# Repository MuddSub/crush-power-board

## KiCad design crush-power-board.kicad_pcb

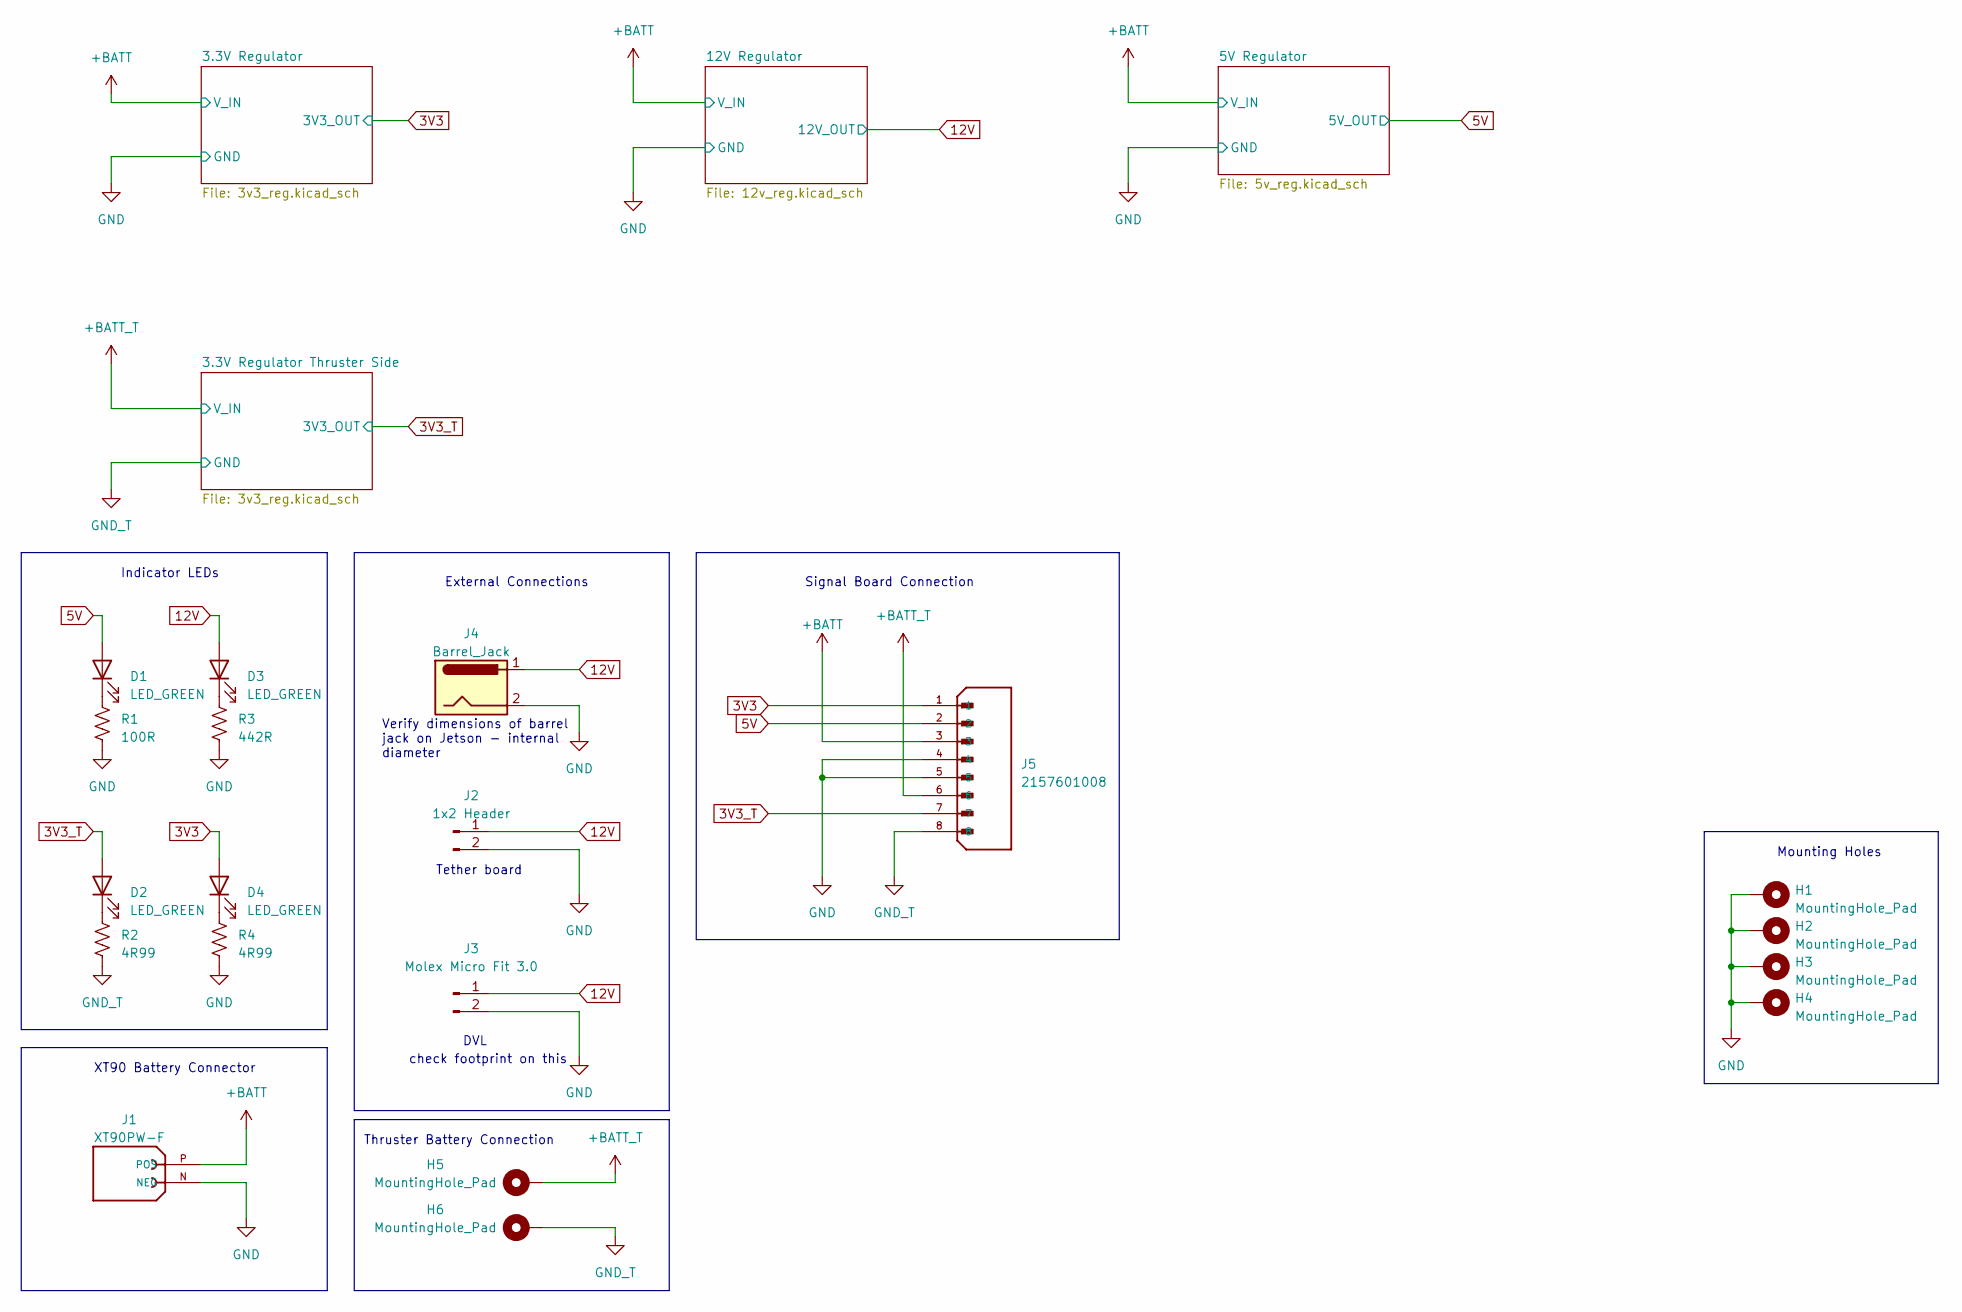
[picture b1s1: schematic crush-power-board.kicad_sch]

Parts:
D1, D2, D3, D4: LED_GREEN; LED_0603_1608Metric
H1, H2, H3, H4: MountingHole_Pad; MountingHole_3.7mm_Pad_Via
H5, H6: MountingHole_Pad; MountingHole_4.5mm_Pad_Via
J1: XT90PW-F; AMASS_XT90PW-F; PARTREV V00
J2: 1x2 Header; PinHeader_1x02_P2.54mm_Vertical
J3: Molex Micro Fit 3.0; Molex_Micro-Fit_3.0_43045-0212_2x01_P3.00mm_Vertical
J4: Barrel_Jack; BarrelJack_Horizontal
J5: 2157601008; MOLEX_2157601008; PARTREV A1
R1: 100R; R_0603_1608Metric
R2, R4: 4R99; R_0603_1608Metric
R3: 442R; R_0603_1608Metric

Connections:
3V3: D4.2 (A), J5.1; also elsewhere on the board
3V3_T: D2.2 (A), J5.7; also elsewhere on the board
5V: D1.2 (A), J5.2; also elsewhere on the board
12V: D3.2 (A), J2.1, J3.1, J4.1; also elsewhere on the board
+BATT: J1.P (POS), J5.3; also elsewhere on the board
+BATT_T: H5.1, J5.6; also elsewhere on the board
GND: H1.1, H2.1, H3.1, H4.1, J1.N (NEG), J2.2, J3.2, J4.2, J5.4, J5.5, R1.2, R3.2, R4.2; also elsewhere on the board
GND1: H6.1, J5.8, R2.2; also elsewhere on the board
unnamed: D1.1 (K), R1.1
unnamed: D2.1 (K), R2.1
unnamed: D3.1 (K), R3.1
unnamed: D4.1 (K), R4.1

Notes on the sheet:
check footprint on this
Indicator LEDs
Mounting Holes
DVL
Signal Board Connection
External Connections
XT90 Battery Connector
Thruster Battery Connection
Verify dimensions of barrel jack on Jetson - internal diameter
Tether board

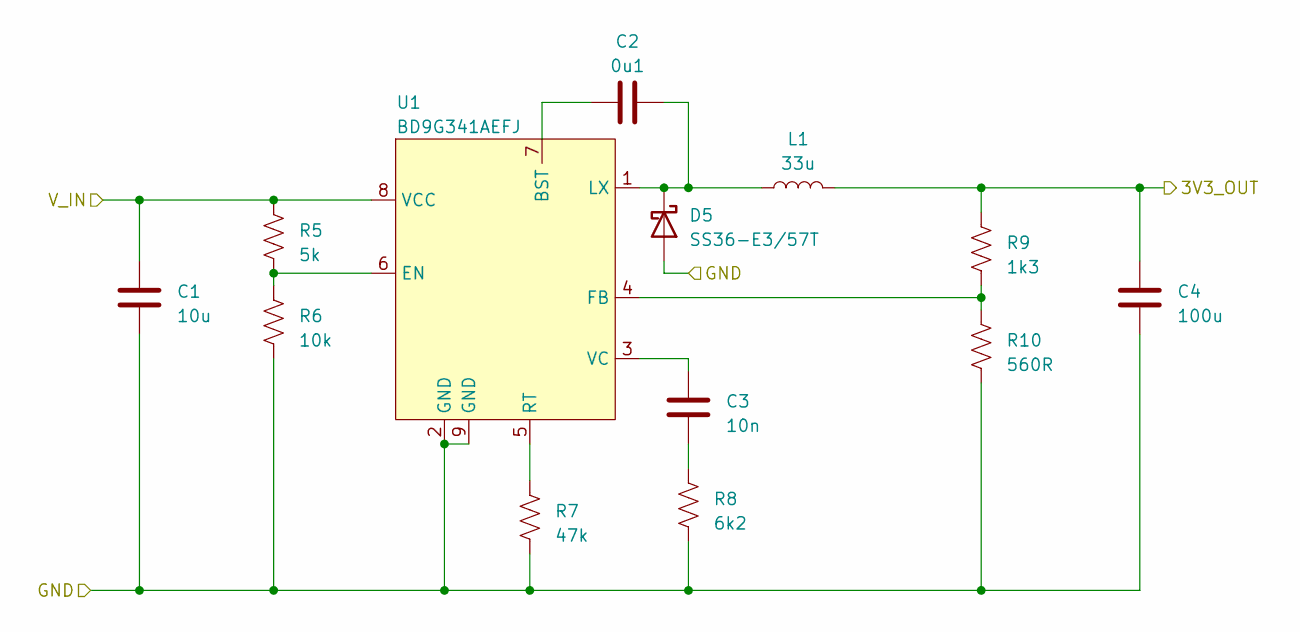
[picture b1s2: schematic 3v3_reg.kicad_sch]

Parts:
C1: 10u; C_0603_1608Metric
C2: 0u1; C_0603_1608Metric
C3: 10n; C_0603_1608Metric
C4: 100u; C_1206_3216Metric
D5: SS36-E3/57T; DIODE_DO214AB
L1: 33u; IND_#B953AS-330M=P3
R5: 5k; R_0603_1608Metric
R6: 10k; R_0603_1608Metric
R7: 47k; R_0603_1608Metric
R8: 6k2; R_0603_1608Metric
R9: 1k3; R_0603_1608Metric
R10: 560R; R_0603_1608Metric
U1: BD9G341AEFJ; SOIC127P600X100-9N

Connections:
3V3: C4.1, L1.2, R9.1; also elsewhere on the board
+BATT: C1.1, R5.1, U1.8 (VCC); also elsewhere on the board
GND: C1.2, C4.2, D5.2 (A), R6.2, R7.2, R8.2, R10.2, U1.2 (GND), U1.9 (GND); also elsewhere on the board
unnamed: C3.2, R8.1
unnamed: C2.2, D5.1 (K), L1.1, U1.1 (LX)
unnamed: C2.1, U1.7 (BST)
unnamed: R5.2, R6.1, U1.6 (EN)
unnamed: R9.2, R10.1, U1.4 (FB)
unnamed: R7.1, U1.5 (RT)
unnamed: C3.1, U1.3 (VC)

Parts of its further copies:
C45: 10u; C_0603_1608Metric
C46: 0u1; C_0603_1608Metric
C47: 10n; C_0603_1608Metric
C48: 100u; C_1206_3216Metric
D6: SS36-E3/57T; DIODE_DO214AB
L4: 33u; IND_#B953AS-330M=P3
R33: 5k; R_0603_1608Metric
R34: 10k; R_0603_1608Metric
R35: 47k; R_0603_1608Metric
R36: 6k2; R_0603_1608Metric
R37: 1k3; R_0603_1608Metric
R38: 560R; R_0603_1608Metric
U4: BD9G341AEFJ; SOIC127P600X100-9N

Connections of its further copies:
3V3_T: C48.1, L4.2, R37.1; also elsewhere on the board
+BATT_T: C45.1, R33.1, U4.8 (VCC); also elsewhere on the board
GND1: C45.2, C48.2, D6.2 (A), R34.2, R35.2, R36.2, R38.2, U4.2 (GND), U4.9 (GND); also elsewhere on the board
unnamed: C47.2, R36.1
unnamed: C46.2, D6.1 (K), L4.1, U4.1 (LX)
unnamed: C46.1, U4.7 (BST)
unnamed: R33.2, R34.1, U4.6 (EN)
unnamed: R37.2, R38.1, U4.4 (FB)
unnamed: R35.1, U4.5 (RT)
unnamed: C47.1, U4.3 (VC)

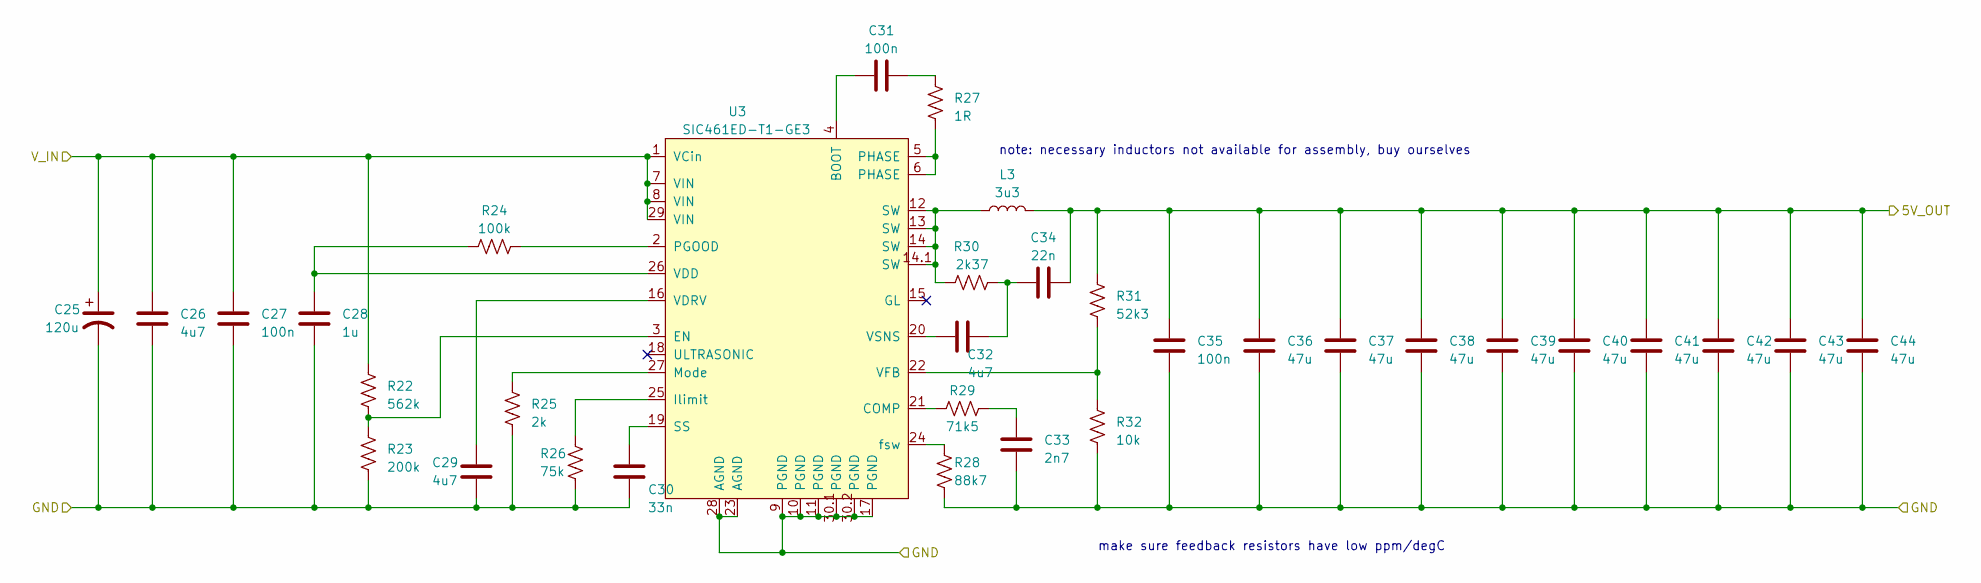
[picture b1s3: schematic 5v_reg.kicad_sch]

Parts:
C25: 120u; CP_Radial_D8.0mm_P3.50mm
C26: 4u7; C_0603_1608Metric
C27, C35: 100n; C_0603_1608Metric
C28: 1u; C_0603_1608Metric
C29, C32: 4u7; C_0805_2012Metric
C30: 33n; C_0603_1608Metric
C31: 100n; C_0402_1005Metric
C33: 2n7; C_0603_1608Metric
C34: 22n; C_0402_1005Metric
C36, C37, C38, C39, C40, C41, C42, C43, C44: 47u; C_1210_3225Metric
L3: 3u3; IND_IHLP-6767GZ_VIS-M
R22: 562k; R_0603_1608Metric
R23: 200k; R_0603_1608Metric
R24: 100k; R_0603_1608Metric
R25: 2k; R_0603_1608Metric
R26: 75k; R_0603_1608Metric
R27: 1R; R_0402_1005Metric
R28: 88k7; R_0603_1608Metric
R29: 71k5; R_0402_1005Metric
R30: 2k37; R_0402_1005Metric
R31: 52k3; R_0603_1608Metric
R32: 10k; R_0603_1608Metric
U3: SIC461ED-T1-GE3; CONV_SIC461ED-T1-GE3; PARTREV M

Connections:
5V: C34.2, C35.1, C36.1, C37.1, C38.1, C39.1, C40.1, C41.1, C42.1, C43.1, C44.1, L3.2, R31.1; also elsewhere on the board
+BATT: C25.1, C26.2, C27.2, R22.2, U3.1 (VCin), U3.7 (VIN), U3.8 (VIN), U3.29 (VIN); also elsewhere on the board
GND: C25.2, C26.1, C27.1, C28.1, C29.1, C30.1, C33.2, C35.2, C36.2, C37.2, C38.2, C39.2, C40.2, C41.2, C42.2, C43.2, C44.2, R23.1, R25.2, R26.2, R28.2, R32.2, U3.9 (PGND), U3.10 (PGND), U3.11 (PGND), U3.17 (PGND), U3.23 (AGND), U3.28 (AGND), U3.30.1 (PGND), U3.30.2 (PGND); also elsewhere on the board
unnamed: C31.2, R27.2
unnamed: C32.2, C34.1, R30.2
unnamed: C33.1, R29.2
unnamed: L3.1, R30.1, U3.12 (SW), U3.13 (SW), U3.14 (SW), U3.14.1 (SW)
unnamed: R27.1, U3.5 (PHASE), U3.6 (PHASE)
unnamed: C31.1, U3.4 (BOOT)
unnamed: R29.1, U3.21 (COMP)
unnamed: R22.1, R23.2, U3.3 (EN)
unnamed: R26.1, U3.25 (Ilimit)
unnamed: R25.1, U3.27 (Mode)
unnamed: R24.2, U3.2 (PGOOD)
unnamed: C30.2, U3.19 (SS)
unnamed: C28.2, R24.1, U3.26 (VDD)
unnamed: C29.2, U3.16 (VDRV)
unnamed: R31.2, R32.1, U3.22 (VFB)
unnamed: C32.1, U3.20 (VSNS)
unnamed: R28.1, U3.24 (fsw)

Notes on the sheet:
make sure feedback resistors have low ppm/degC
note: necessary inductors not available for assembly, buy ourselves

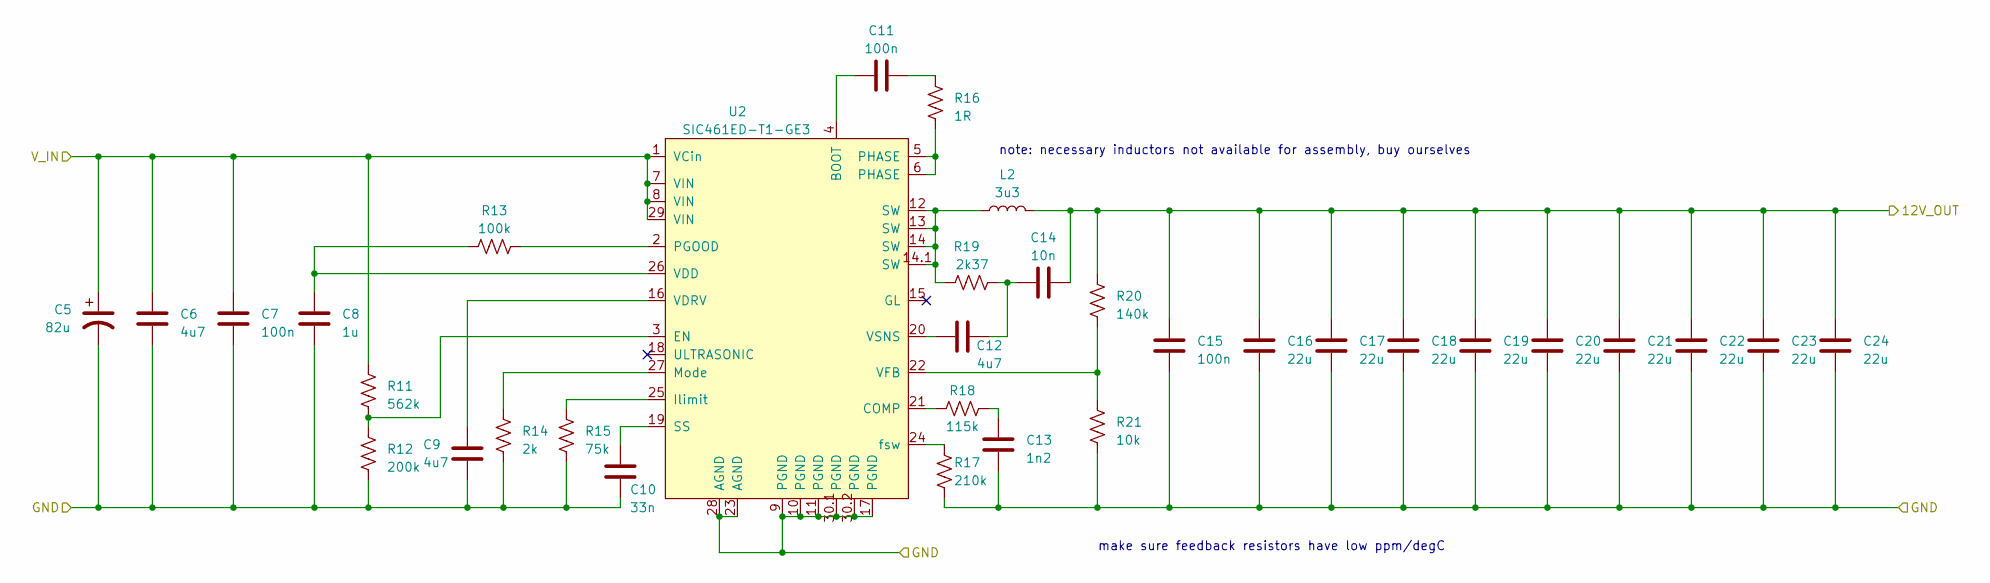
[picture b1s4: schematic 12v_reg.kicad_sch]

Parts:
C5: 82u; CP_Radial_D8.0mm_P3.50mm
C6: 4u7; C_0603_1608Metric
C7, C15: 100n; C_0603_1608Metric
C8: 1u; C_0603_1608Metric
C9, C12: 4u7; C_0805_2012Metric
C10: 33n; C_0603_1608Metric
C11: 100n; C_0402_1005Metric
C13: 1n2; C_0603_1608Metric
C14: 10n; C_0402_1005Metric
C16, C17, C18, C19, C20, C21, C22, C23, C24: 22u; C_1210_3225Metric
L2: 3u3; IND_IHLP-6767GZ_VIS-M
R11: 562k; R_0603_1608Metric
R12: 200k; R_0603_1608Metric
R13: 100k; R_0603_1608Metric
R14: 2k; R_0603_1608Metric
R15: 75k; R_0603_1608Metric
R16: 1R; R_0402_1005Metric
R17: 210k; R_0603_1608Metric
R18: 115k; R_0402_1005Metric
R19: 2k37; R_0402_1005Metric
R20: 140k; R_0603_1608Metric
R21: 10k; R_0603_1608Metric
U2: SIC461ED-T1-GE3; CONV_SIC461ED-T1-GE3; PARTREV M

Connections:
12V: C14.2, C15.1, C16.1, C17.1, C18.1, C19.1, C20.1, C21.1, C22.1, C23.1, C24.1, L2.2, R20.1; also elsewhere on the board
+BATT: C5.1, C6.2, C7.2, R11.2, U2.1 (VCin), U2.7 (VIN), U2.8 (VIN), U2.29 (VIN); also elsewhere on the board
GND: C5.2, C6.1, C7.1, C8.1, C9.1, C10.1, C13.2, C15.2, C16.2, C17.2, C18.2, C19.2, C20.2, C21.2, C22.2, C23.2, C24.2, R12.1, R14.2, R15.2, R17.2, R21.2, U2.9 (PGND), U2.10 (PGND), U2.11 (PGND), U2.17 (PGND), U2.23 (AGND), U2.28 (AGND), U2.30.1 (PGND), U2.30.2 (PGND); also elsewhere on the board
unnamed: C11.2, R16.2
unnamed: C12.2, C14.1, R19.2
unnamed: C13.1, R18.2
unnamed: L2.1, R19.1, U2.12 (SW), U2.13 (SW), U2.14 (SW), U2.14.1 (SW)
unnamed: R16.1, U2.5 (PHASE), U2.6 (PHASE)
unnamed: C11.1, U2.4 (BOOT)
unnamed: R18.1, U2.21 (COMP)
unnamed: R11.1, R12.2, U2.3 (EN)
unnamed: R15.1, U2.25 (Ilimit)
unnamed: R14.1, U2.27 (Mode)
unnamed: R13.2, U2.2 (PGOOD)
unnamed: C10.2, U2.19 (SS)
unnamed: C8.2, R13.1, U2.26 (VDD)
unnamed: C9.2, U2.16 (VDRV)
unnamed: R20.2, R21.1, U2.22 (VFB)
unnamed: C12.1, U2.20 (VSNS)
unnamed: R17.1, U2.24 (fsw)

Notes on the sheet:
note: necessary inductors not available for assembly, buy ourselves
make sure feedback resistors have low ppm/degC

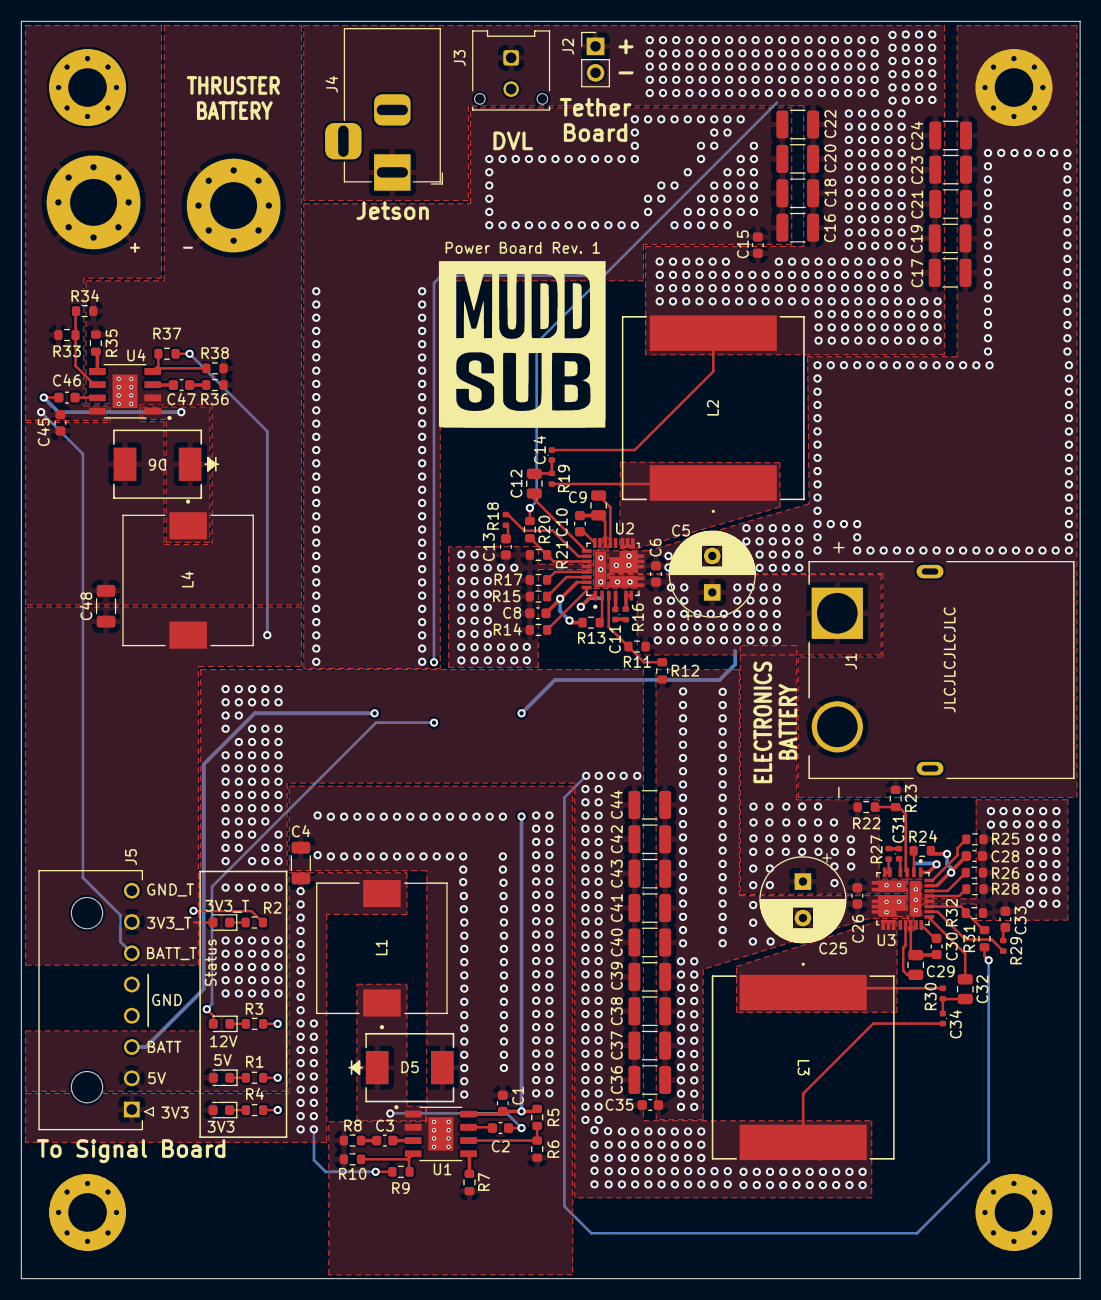
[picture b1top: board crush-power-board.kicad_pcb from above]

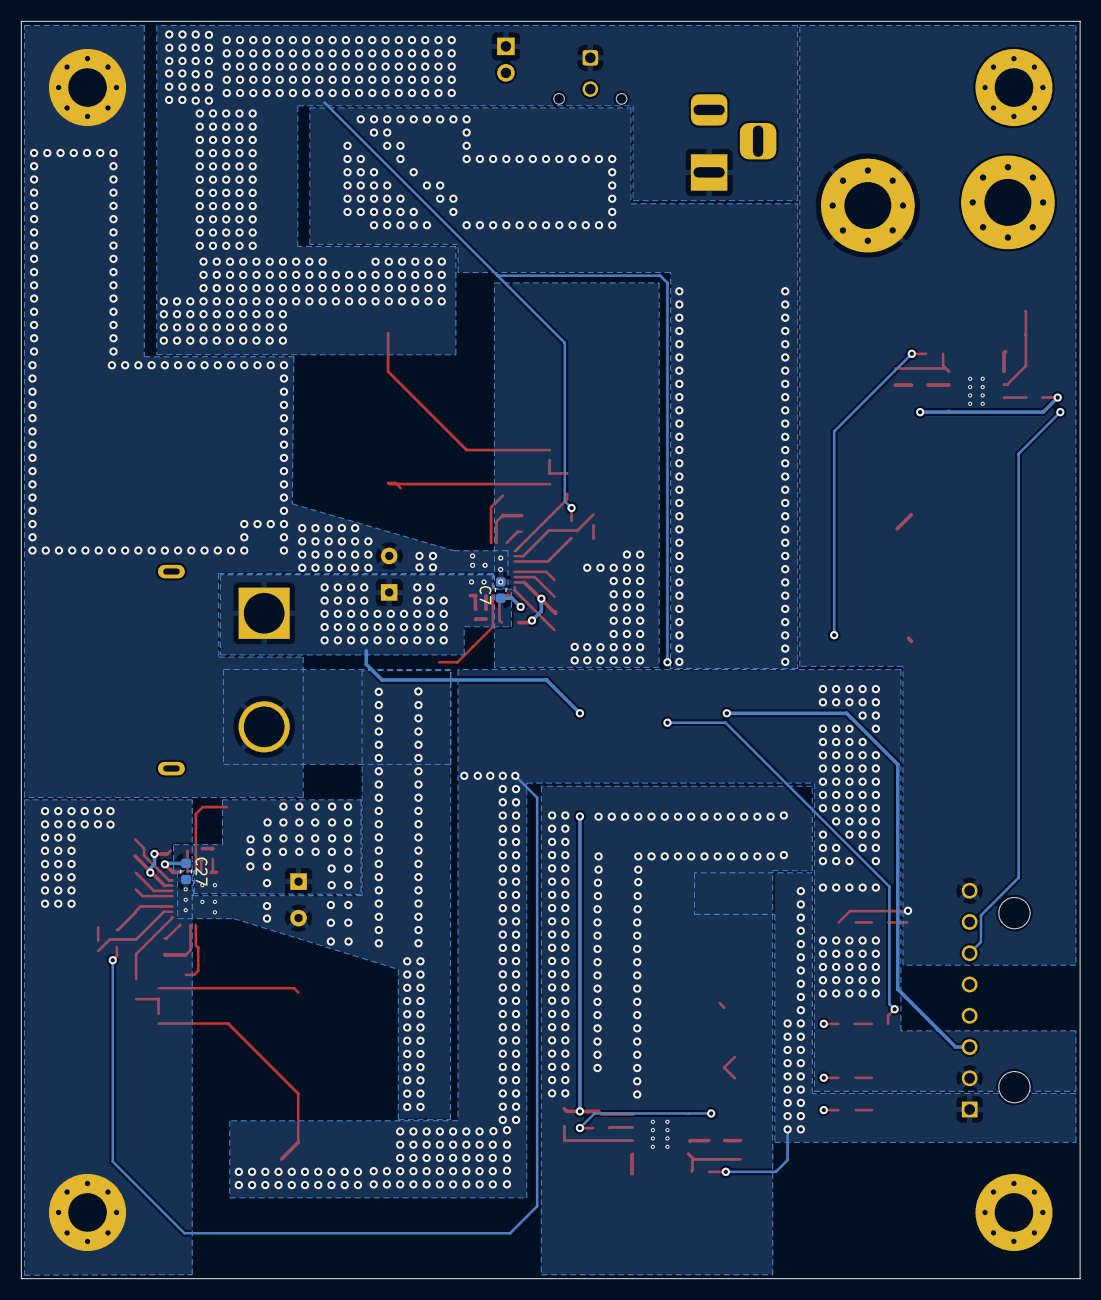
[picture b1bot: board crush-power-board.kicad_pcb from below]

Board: 4 copper layers, 101.6 x 120.6 mm, 111 parts (2 on the bottom side), 60 nets.

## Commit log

2023-03-26 minor change
2023-03-26 added all power regulator circuits
2023-04-02 Added component values for the 3V3 regulator, cleaned up some schematics
2023-04-08 Added values to components
2023-04-09 Changed 3.3V Regulator, as well as added hierarchical elements to schematic
2023-04-09 Added hierarchical schematics
2023-04-09 Changed 12V Regulator values, added thruster side 3V3 regulator
2023-04-09 removed autosaved files
2023-04-10 Added extra output capacitance to 12V regulator, added component designators
2023-04-10 Added more component footprints
2023-04-16 Fixed a lot of components
2023-04-17 Added extra footprints for diodes and capacitors
2023-04-17 Fixed reference designators
2023-04-19 Added indicator LEDs and fixed some footprints
2023-04-19 fixed some more footprints for resistors. 0201 -> 0603
2023-04-19 Changed boot/phase resistor and cap to be 0402 package according to SiC467 datasheet
2023-04-19 fixed some routing for 3v3 regulator
2023-04-21 Added connections to signal board, battery, and mounting holes
2023-04-21 Added new connectors to library and updated gitignore
2023-04-22 Changed 5V regulator and 12V regulator to the SiC461. Both support 10A and 5V and 12V respectively
2023-04-23 started pcb layout
2023-04-23 Changed schottky diode for 3.3V regulator
2023-04-23 updated pcb layout
2023-04-24 Added more to the layout of the 12V regulator as well as changed some capacitor footprints
2023-05-18 Finished layout for 12V regulator
2023-05-18 Added thermal vias to the 12V regulator, fixed GND pad nets on 12V and 5V regulator
2023-08-12 Added local config file to gitignore
2023-09-23 change power board to 4 layers
2024-02-17 Added DRC import for JLCPCB
2024-03-11 route 3v3 regulator
2024-03-11 switch inner routing to back plane
2024-03-11 add missing wire
2024-03-11 fix batt_t planes
2024-03-11 add 5v routing
2024-03-11 route 5v regulator
2024-03-11 route 3v3_T regulator
2024-03-11 move feedback trace to back layer
2024-03-11 Added more vias and plane differences to 5V reg
2024-03-11 add missing vias
2024-03-11 start 12v routing
2024-03-11 run drc
2024-03-12 finish main 12v layout
2024-03-12 fix drc violations
2024-03-12 preparing for board layout
2024-03-14 layout majority of power board
2024-03-14 drc fixes and update schematic to reflect correct ic footprints
2024-03-14 realign zone boundaries
2024-03-14 move traces
2024-03-14 vias and silkscreen
2024-03-16 fix signal board connector orientation
2024-03-16 finish signal board connector routing
2024-03-16 resize zones
2024-03-17 3v3_t routing
2024-03-23 misc design fixes
2024-03-23 fix silkscreen drc violations
2024-04-06 update board size
2024-04-06 added mounting holes
2024-04-06 fix mounting hole alignment
2024-04-06 increase 12v plane size
2024-04-08 use 6-32 mounting holes
2024-04-27 label 12v status indicator
2024-04-27 cleanup traces/vias
2024-05-04 Silkscreen changes
2024-05-04 added JLC order number placement
2024-09-18 add thruster battery connection
2024-09-21 add codeowners file
2024-09-21 update for 8-32 screws
2024-09-23 remove unnecessary silkscreen text
2024-11-02 use 4u7 capacitors for vsns pins
2024-11-16 fix footprint on 3v3 output capacitors
2025-11-03 Removing vias
2026-04-11 Added -5V voltage source using 5V regulator, also fixed 3V3 output pins on 3V3 regulator subsheets
